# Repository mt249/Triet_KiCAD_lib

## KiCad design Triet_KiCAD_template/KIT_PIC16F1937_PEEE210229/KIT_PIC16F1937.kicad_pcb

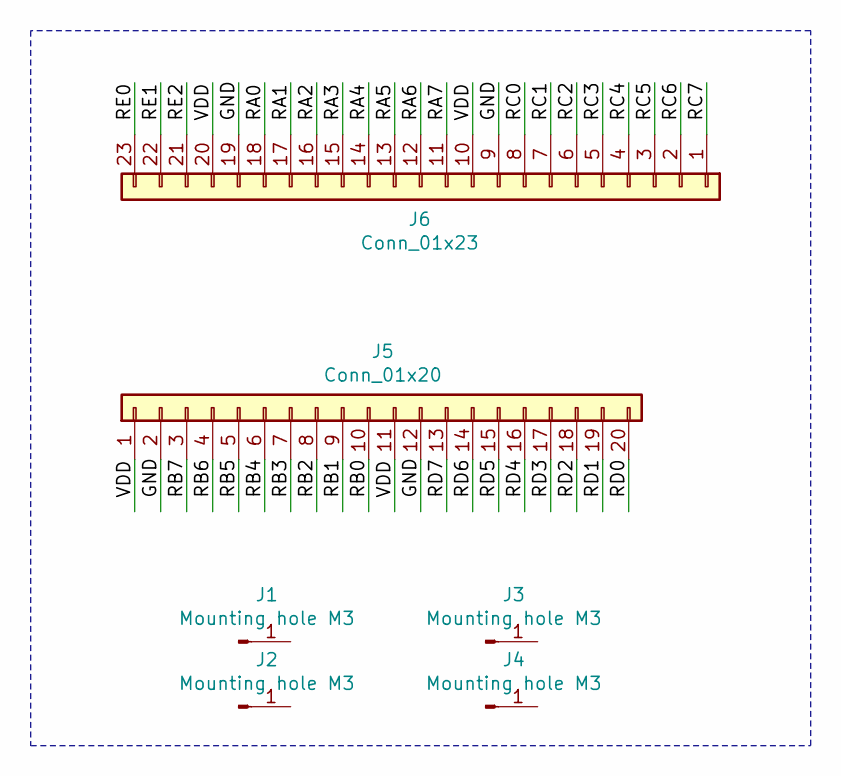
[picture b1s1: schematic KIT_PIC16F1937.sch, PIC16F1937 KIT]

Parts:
J1, J2, J3, J4: Mounting hole M3; MountingHole_2.5mm_Pad_Via
J5: Conn_01x20; PinHeader_1x20_P2.54mm_Vertical
J6: Conn_01x23; PinSocket_1x23_P2.54mm_Vertical

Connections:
/GND: J5.2, J5.12, J6.9, J6.19
/RA0: J6.18
/RA1: J6.17
/RA2: J6.16
/RA3: J6.15
/RA4: J6.14
/RA5: J6.13
/RA6: J6.12
/RA7: J6.11
/RB0: J5.10
/RB1: J5.9
/RB2: J5.8
/RB3: J5.7
/RB4: J5.6
/RB5: J5.5
/RB6: J5.4
/RB7: J5.3
/RC0: J6.8
/RC1: J6.7
/RC2: J6.6
/RC3: J6.5
/RC4: J6.4
/RC5: J6.3
/RC6: J6.2
/RC7: J6.1
/RD0: J5.20
/RD1: J5.19
/RD2: J5.18
/RD3: J5.17
/RD4: J5.16
/RD5: J5.15
/RD6: J5.14
/RD7: J5.13
/RE0: J6.23
/RE1: J6.22
/RE2: J6.21
/VDD: J5.1, J5.11, J6.10, J6.20

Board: 2 copper layers, 6 parts (0 on the bottom side), 2 nets, no tracks yet.
